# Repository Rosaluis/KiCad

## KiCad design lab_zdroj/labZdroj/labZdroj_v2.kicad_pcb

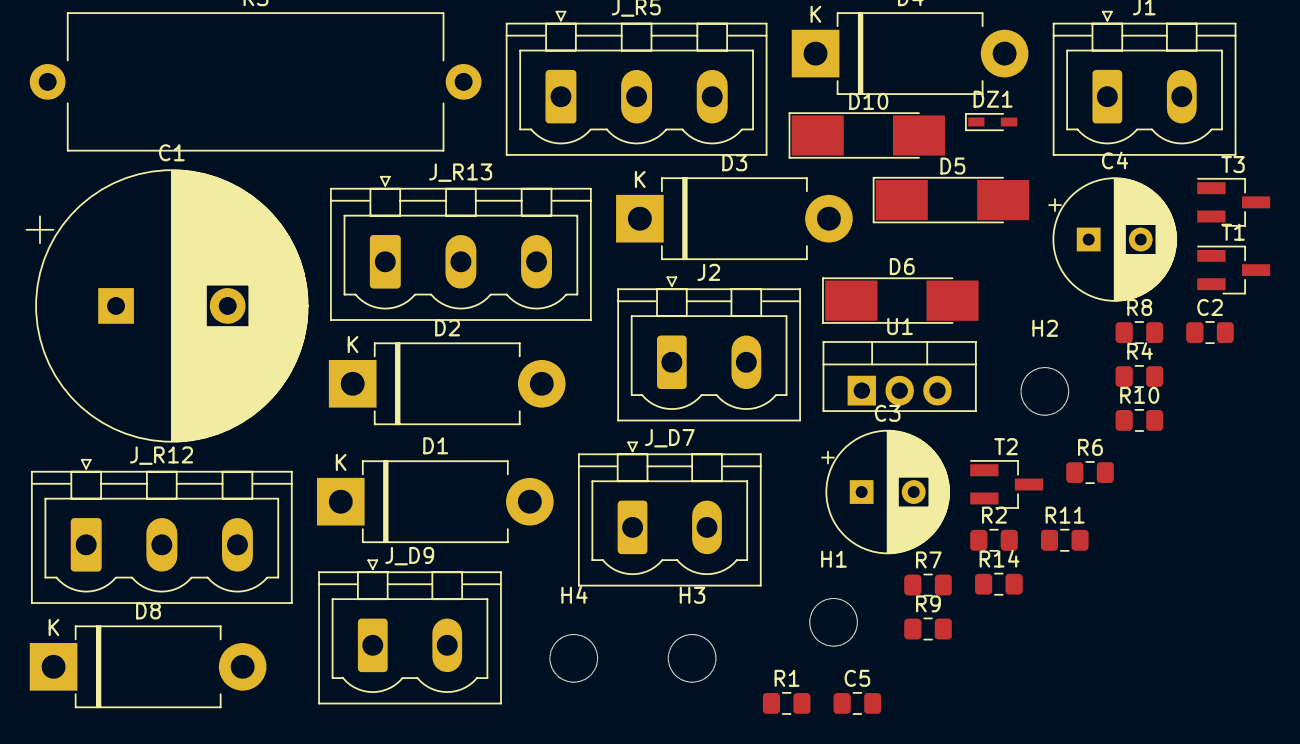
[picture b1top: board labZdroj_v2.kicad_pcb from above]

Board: 2 copper layers, 40 parts (0 on the bottom side), 21 nets, no tracks yet.

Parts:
C1: 4m7; CP_Radial_D18.0mm_P7.50mm
C2, C5: 100n; C_0805_2012Metric_Pad1.15x1.40mm_HandSolder
C3, C4: 100u; CP_Radial_D8.0mm_P3.50mm
D1, D2, D3, D4, D8: BY550; D_DO-201AD_P12.70mm_Horizontal
D5, D6, D10: 1N4007; D_MELF_Handsoldering
DZ1: 4V1; D_SC-80_HandSoldering
H1, H2, H3, H4: MountingHole; MountingHole_3.2mm_M3
J1: 24V st; PhoenixContact_MSTBVA_2,5_2-G_1x02_P5.00mm_Vertical
J2: 0-30V ss; PhoenixContact_MSTBVA_2,5_2-G_1x02_P5.00mm_Vertical
J_D7: green_LED; PhoenixContact_MSTBVA_2,5_2-G_1x02_P5.00mm_Vertical
J_D9: red_LED; PhoenixContact_MSTBVA_2,5_2-G_1x02_P5.00mm_Vertical
J_R5: 1k; PhoenixContact_MSTBVA_2,5_3-G-5,08_1x03_P5.08mm_Vertical
J_R12: 100k; PhoenixContact_MSTBVA_2,5_3-G-5,08_1x03_P5.08mm_Vertical
J_R13: 5k; PhoenixContact_MSTBVA_2,5_3-G-5,08_1x03_P5.08mm_Vertical
R1, R2, R7: 2k7; R_0805_2012Metric_Pad1.15x1.40mm_HandSolder
R3: 0R27; R_Axial_Power_L25.0mm_W9.0mm_P27.94mm
R4: 680R; R_0805_2012Metric_Pad1.15x1.40mm_HandSolder
R6, R9: 30k; R_0805_2012Metric_Pad1.15x1.40mm_HandSolder
R8, R10: 220R; R_0805_2012Metric_Pad1.15x1.40mm_HandSolder
R11: 4k7; R_0805_2012Metric_Pad1.15x1.40mm_HandSolder
R14: 1k2; R_0805_2012Metric_Pad1.15x1.40mm_HandSolder
T1: BC327; SOT-23_Handsoldering
T2, T3: BC547; SOT-23_Handsoldering
U1: LM350_TO220; TO-220-3_Vertical

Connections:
+24V: C1.1, C2.1, D1.1, D2.1, J_R5.3, R1.1, R3.2, R9.2
GND: C1.2, C2.2, C3.1, C5.2, D3.2, D4.2, DZ1.1, J2.1, R1.2, R14.2
unnamed: C3.2, D6.2, R2.2
unnamed: C4.1, D2.2, D3.1, J1.2
unnamed: C4.2, D5.2, D6.1
unnamed: C5.1, D10.2, J2.2, R11.1, R14.1, U1.2
unnamed: D1.2, D4.1, D5.1, J1.1
unnamed: D8.2, R3.1
unnamed: D8.1, D10.1, R4.1, T1.2, U1.3
unnamed: DZ1.2, J_D7.1
unnamed: J_D7.2, J_R13.2, J_R13.3, R2.1, R7.2, T2.3, T3.3
unnamed: J_D9.1, T2.1
unnamed: J_D9.2, R9.1
unnamed: J_R5.1, R4.2
unnamed: J_R5.2, T1.3
unnamed: J_R12.1, R11.2, T3.1, U1.1
unnamed: J_R12.2, J_R12.3, J_R13.1
unnamed: R6.2, T1.1
unnamed: R8.1, T2.2
unnamed: R10.1, T3.2
unnamed: R6.1, R7.1, R8.2, R10.2

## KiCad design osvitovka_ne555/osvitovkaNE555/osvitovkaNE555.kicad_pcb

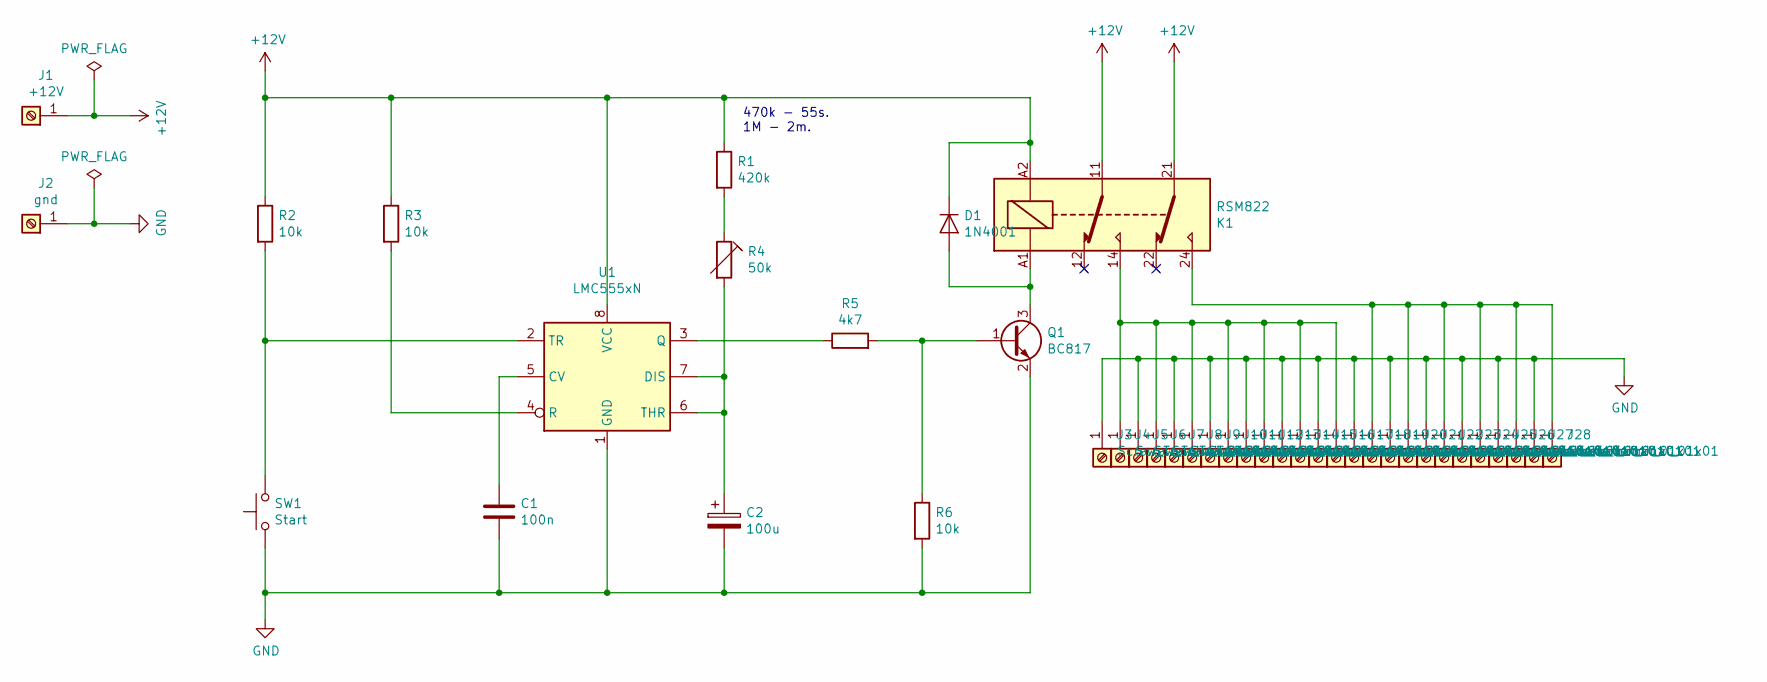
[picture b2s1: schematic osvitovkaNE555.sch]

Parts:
C1: 100n; C_Disc_D3.0mm_W1.6mm_P2.50mm
C2: 100u; CP_Radial_D6.3mm_P2.50mm
D1: 1N4001; D_1206_3216Metric
J1: +12V; SolderWirePad_1x01_Drill1.2mm
J2: gnd; SolderWirePad_1x01_Drill1.2mm
J3, J4, J5, J6, J7, J8, J9, J10, J11, J12, J13, J14, J15, J16, J17, J18, J19, J20, J21, J22, J23, J24, J25, J26, J27, J28: Screw_Terminal_01x01; TestPoint_THTPad_D3.0mm_Drill1.5mm
K1: RSM822; Relay_DPDT_Finder_30.22
Q1: BC817; SOT-23
R1: 420k; R_0805_2012Metric
R2, R3, R6: 10k; R_0805_2012Metric
R4: 50k; Potentiometer_Runtron_RM-063_Horizontal
R5: 4k7; R_0805_2012Metric
SW1: Start; SW_PUSH_6mm_H8mm
U1: LMC555xN; DIP-8_W7.62mm

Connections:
+12V: D1.1 (K), J1.1, K1.11, K1.21, K1.A2, R1.1, R2.1, R3.1, U1.8 (VCC)
GND: C1.2, C2.2, J2.1, J3.1, J5.1, J7.1, J9.1, J11.1, J13.1, J15.1, J17.1, J19.1, J21.1, J23.1, J25.1, J27.1, Q1.2 (E), R6.2, SW1.1, U1.1 (GND)
unnamed: C1.1, U1.5 (CV)
unnamed: C2.1, R4.2, U1.6 (THR), U1.7 (DIS)
unnamed: D1.2 (A), K1.A1, Q1.3 (C)
unnamed: J4.1, J6.1, J8.1, J10.1, J12.1, J14.1, J16.1, K1.14
unnamed: J18.1, J20.1, J22.1, J24.1, J26.1, J28.1, K1.24
unnamed: Q1.1 (B), R5.2, R6.1
unnamed: R1.2, R4.1
unnamed: R2.2, SW1.2, U1.2 (TR)
unnamed: R3.2, U1.4 (R)
unnamed: R5.1, U1.3 (Q)

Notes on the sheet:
470k - 55s. 1M - 2m.

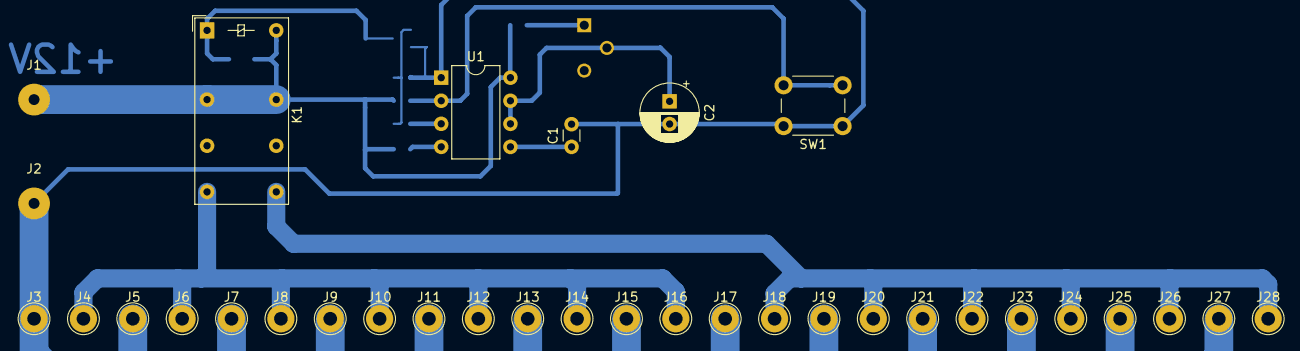
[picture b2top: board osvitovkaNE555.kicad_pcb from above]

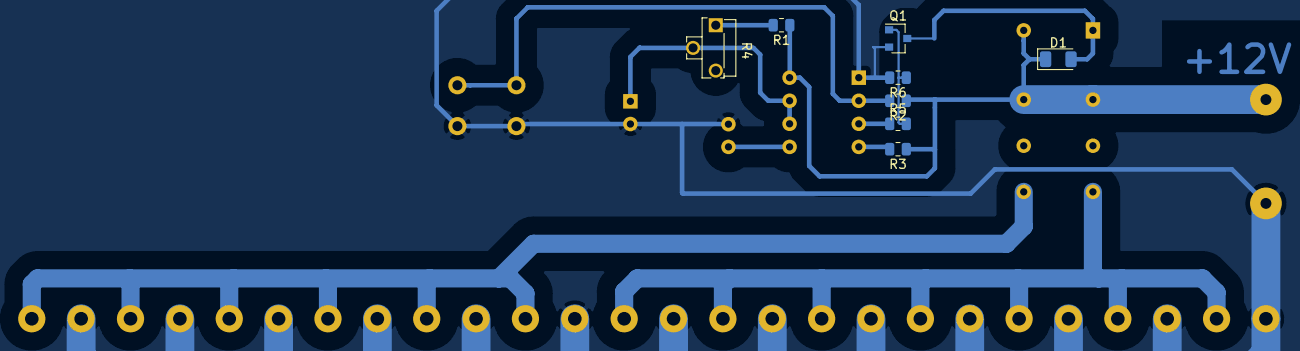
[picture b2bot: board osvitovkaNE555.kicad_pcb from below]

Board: 2 copper layers, 41 parts (8 on the bottom side), 12 nets.

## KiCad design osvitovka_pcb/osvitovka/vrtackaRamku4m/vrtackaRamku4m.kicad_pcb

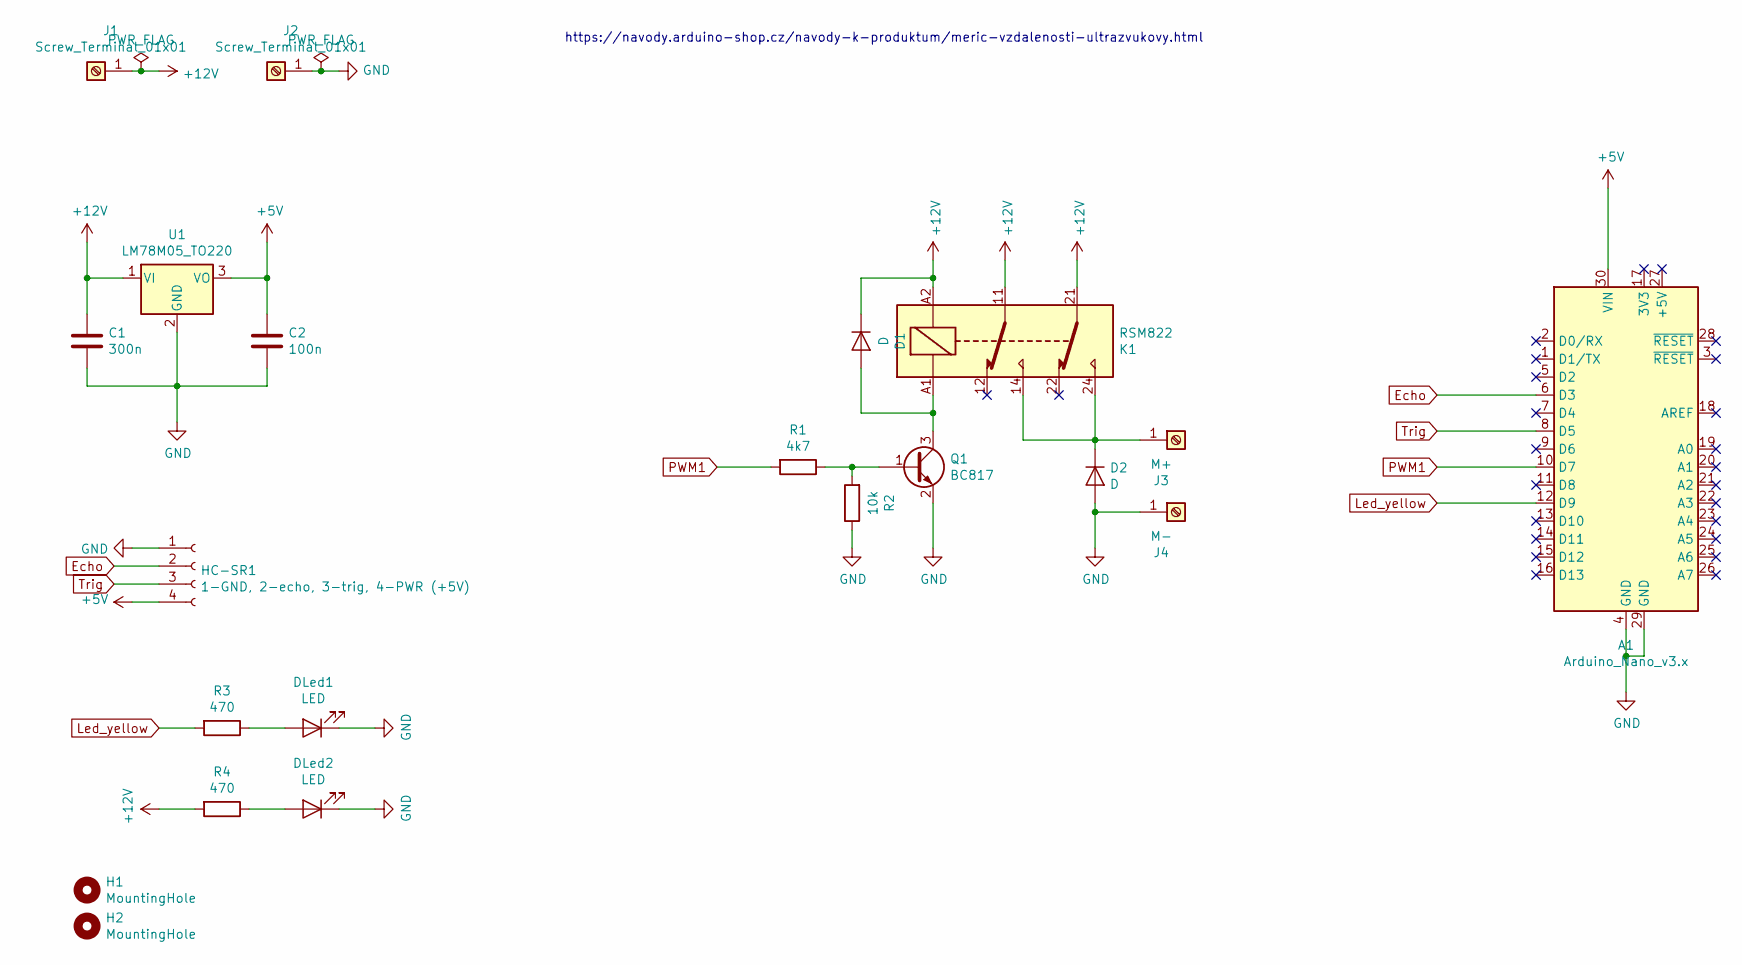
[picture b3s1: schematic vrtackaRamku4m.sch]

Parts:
A1: Arduino_Nano_v3.x; Arduino_Nano_vetsi_plosky
C1: 300n; AR_C_Disc_D3.0mm_W2.0mm_P2.50mm
C2: 100n; AR_C_Disc_D3.0mm_W2.0mm_P2.50mm
D1, D2: D; D_2010_5025Metric_Pad1.52x2.65mm_HandSolder
DLed1, DLed2: LED; AR_LED_D3.0mm
H1, H2: MountingHole; MountingHole_3.2mm_M3_ISO14580
HC-SR1: 1-GND, 2-echo, 3-trig, 4-PWR (+5V); AR_PinHeader_1x04_P2.54mm_Vertical
J1, J2: Screw_Terminal_01x01; TestPoint_Loop_D3.80mm_Drill2.5mm
J3: M+; TestPoint_Loop_D3.80mm_Drill2.5mm
J4: M-; TestPoint_Loop_D3.80mm_Drill2.5mm
K1: RSM822; AR_Relay_DPDT_Finder_30.22
Q1: BC817; SOT-23
R1: 4k7; R_0805_2012Metric
R2: 10k; R_0805_2012Metric
R3, R4: 470; R_0805_2012Metric
U1: LM78M05_TO220; AR_TO-220-3_Vertical

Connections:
+5V: A1.30 (VIN), C2.1, HC-SR1.4, U1.3 (VO)
+12V: C1.1, D1.1 (K), J1.1, K1.11, K1.21, K1.A2, R4.2, U1.1 (VI)
Echo: A1.6 (D3), HC-SR1.2
GND: A1.4 (GND), A1.29 (GND), C1.2, C2.2, D2.2 (A), DLed1.1 (K), DLed2.1 (K), HC-SR1.1, J2.1, J4.1, Q1.2 (E), R2.1, U1.2 (GND)
Led_yellow: A1.12 (D9), R3.2
unnamed: D1.2 (A), K1.A1, Q1.3 (C)
unnamed: D2.1 (K), J3.1, K1.14, K1.24
unnamed: DLed1.2 (A), R3.1
unnamed: DLed2.2 (A), R4.1
unnamed: Q1.1 (B), R1.1, R2.2
PWM1: A1.10 (D7), R1.2
Trig: A1.8 (D5), HC-SR1.3

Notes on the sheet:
https://navody.arduino-shop.cz/navody-k-produktum/meric-vzdalenosti-ultrazvukovy.html

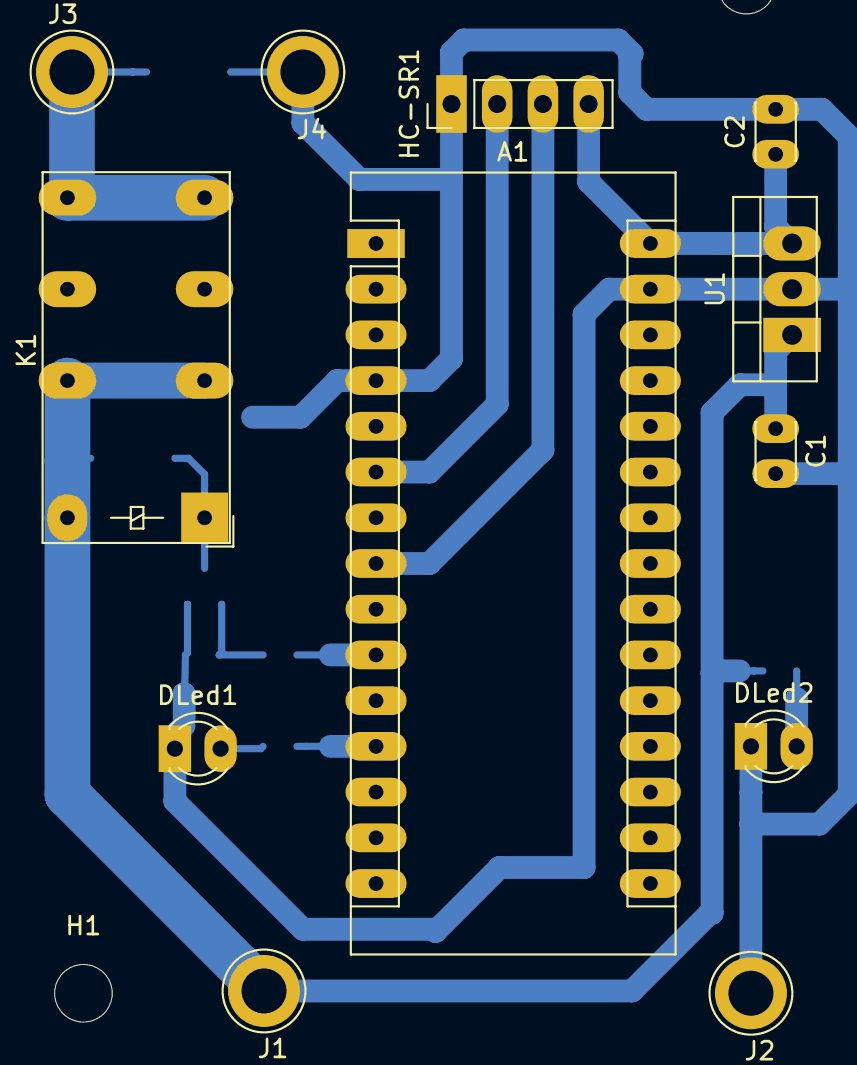
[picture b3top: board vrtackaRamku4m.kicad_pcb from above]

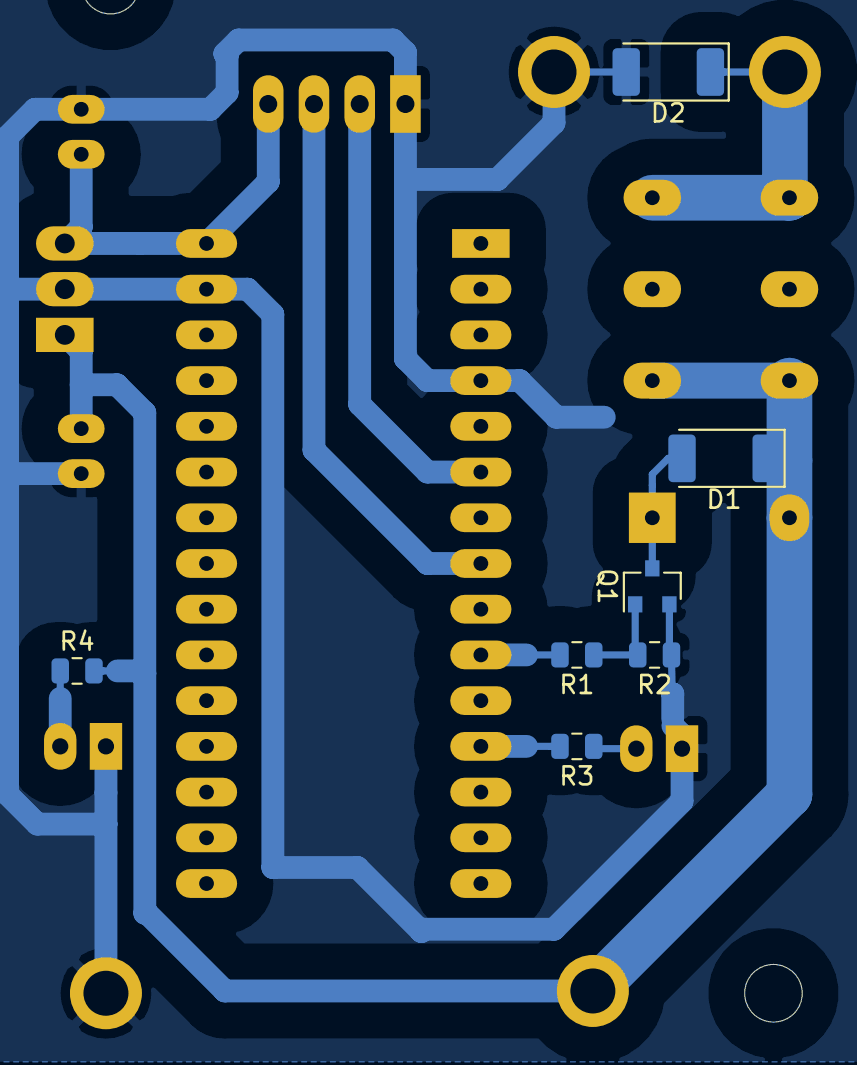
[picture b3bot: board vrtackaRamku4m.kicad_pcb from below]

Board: 2 copper layers, 21 parts (7 on the bottom side), 12 nets.

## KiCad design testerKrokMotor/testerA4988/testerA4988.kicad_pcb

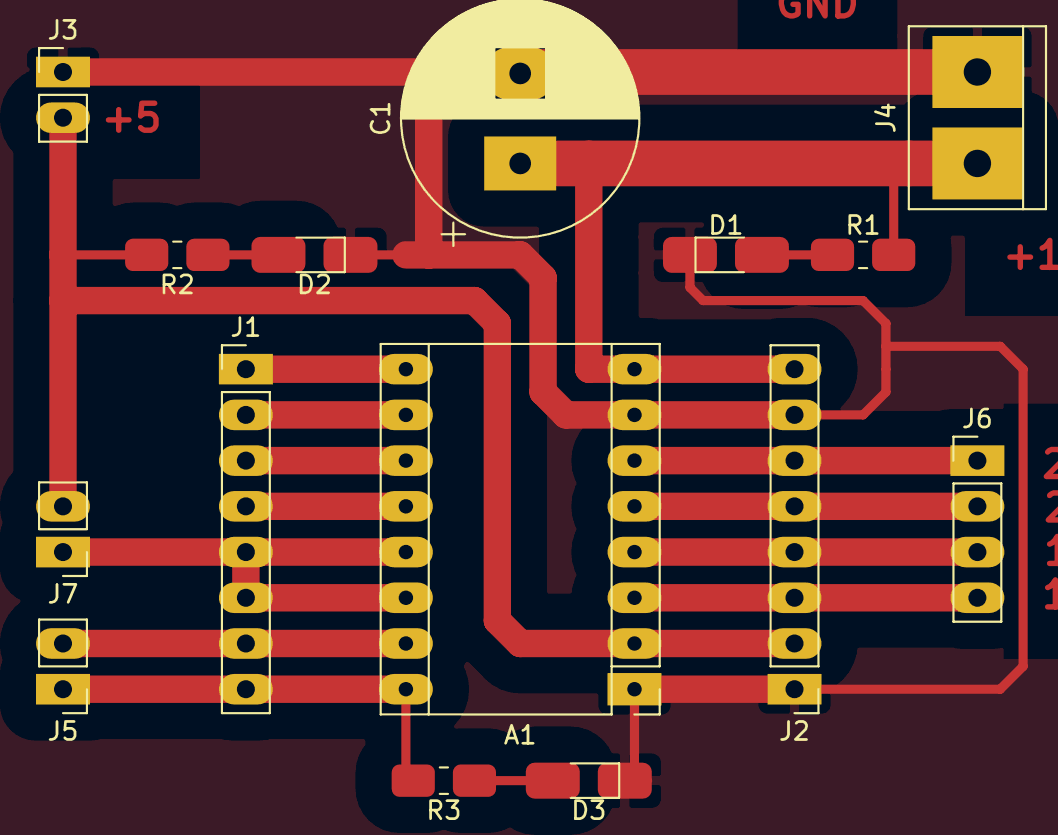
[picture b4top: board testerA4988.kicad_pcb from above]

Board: 2 copper layers, 15 parts (0 on the bottom side), 17 nets.

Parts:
A1: Pololu_Breakout_A4988; AR_Pololu_Breakout-16_15.2x20.3mm
C1: CP; AR_CP_Radial_D13.0mm_P5.00mm
D1, D2, D3: LED; AR_LED_0805_2012Metric
J1, J2: Conn_01x08_Female; AR_PinHeader_1x08_P2.54mm_Vertical
J3, J5, J7: Conn_01x02_Female; AR_PinHeader_1x02_P2.54mm_Vertical
J4: Screw_Terminal_01x02; AR_TerminalBlock_bornier-2_P5.08mm
J6: Conn_01x04_Male; AR_PinHeader_1x04_P2.54mm_Vertical
R1: 1k; AR_R_0805_2012Metric
R2, R3: 200; AR_R_0805_2012Metric

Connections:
+5V: A1.2, J2.2, J3.2, J7.2, R2.2
+12V: A1.8, C1.1, J2.8, J4.1, R1.2
GND: A1.1, A1.7, C1.2, D1.1, D2.1, D3.1, J2.1, J2.7, J3.1, J4.2
unnamed: A1.3, J2.3, J6.4
unnamed: A1.4, J2.4, J6.3
unnamed: A1.5, J2.5, J6.2
unnamed: A1.6, J2.6, J6.1
unnamed: A1.9, J1.1
unnamed: A1.10, J1.2
unnamed: A1.11, J1.3
unnamed: A1.12, J1.4
unnamed: A1.13, A1.14, J1.5, J1.6, J7.1
unnamed: A1.15, J1.7, J5.2
unnamed: A1.16, J1.8, J5.1, R3.2
unnamed: D1.2, R1.1
unnamed: D2.2, R2.1
unnamed: D3.2, R3.1

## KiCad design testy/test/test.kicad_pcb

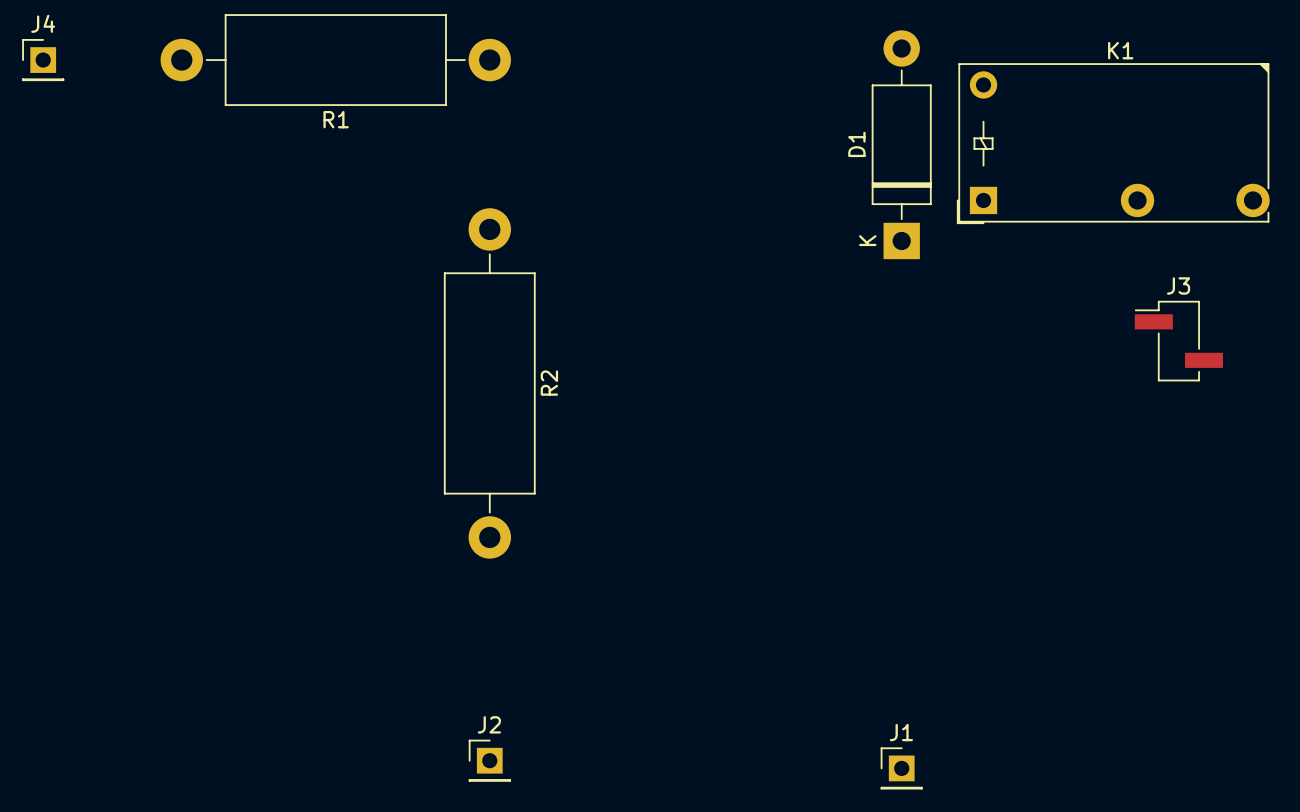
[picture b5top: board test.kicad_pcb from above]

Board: 2 copper layers, 9 parts (1 on the bottom side), 7 nets, no tracks yet.

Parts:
D1: D; D_DO-15_P12.70mm_Horizontal
J1, J2, J4: Conn_01x01_Male; PinHeader_1x01_P2.54mm_Vertical
J3: Conn_01x02_Male; PinHeader_1x02_P2.54mm_Vertical_SMD_Pin1Left
K1: FINDER-32.21-x300; Relay_SPST_Finder_32.21-x300
Q1: BC817; SOT-23W
R1, R2: R; R_Axial_DIN0614_L14.3mm_D5.7mm_P20.32mm_Horizontal

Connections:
+12V: D1.1, J1.1, K1.A1
GND: J2.1, Q1.2, R2.2
unnamed: D1.2, K1.A2, Q1.3
unnamed: J3.1, K1.11
unnamed: J3.2, K1.14
unnamed: J4.1, R1.2
unnamed: Q1.1, R1.1, R2.1
